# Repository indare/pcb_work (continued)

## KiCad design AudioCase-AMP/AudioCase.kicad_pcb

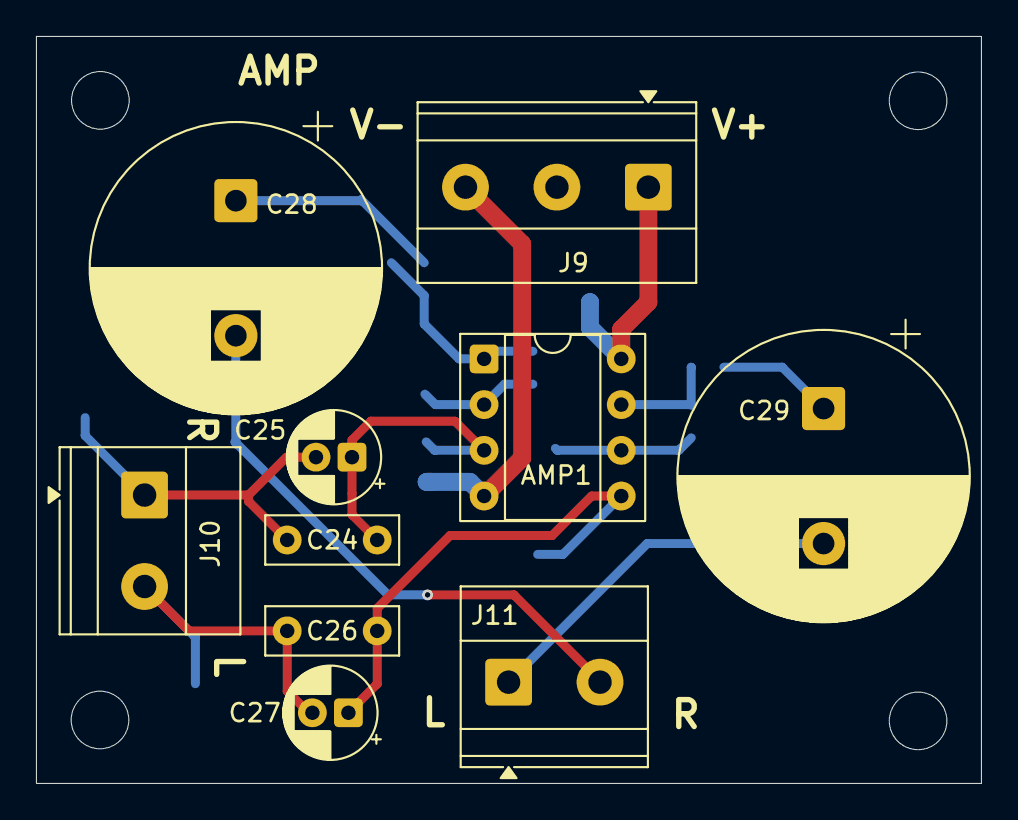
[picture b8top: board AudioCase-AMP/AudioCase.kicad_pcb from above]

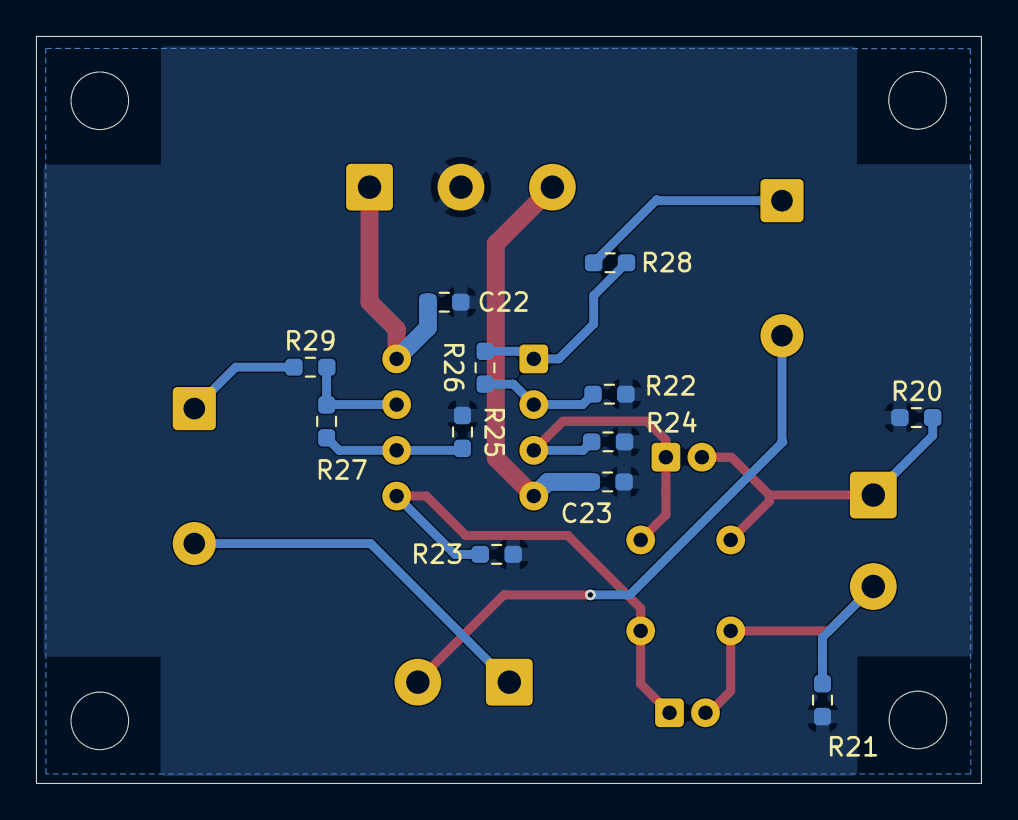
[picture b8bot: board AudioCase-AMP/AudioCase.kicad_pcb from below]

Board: 2 copper layers, 52.5 x 41.5 mm, 26 parts (12 on the bottom side), 15 nets.

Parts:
AMP1: NE5532; DIP-8_W7.62mm_Socket
C22, C23: 0.1μF; R_0603_1608Metric_Pad0.98x0.95mm_HandSolder
C24, C26: 0.1μF; C_Rect_L7.2mm_W2.5mm_P5.00mm_FKS2_FKP2_MKS2_MKP2
C25, C27: 10μF; CP_Radial_D5.0mm_P2.00mm
C28, C29: 470μF; CP_Radial_D16.0mm_P7.50mm
H5, H6, H7, H8: MountingHole; MountingHole_3.2mm_M3
J9: AMP_PWR; TerminalBlock_Phoenix_MKDS-1,5-3-5.08_1x03_P5.08mm_Horizont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
J10: AMP_AUX_IN; TerminalBlock_Phoenix_MKDS-1,5-2-5.08_1x02_P5.08mm_Horizont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
J11: AMP_AUX_OUT; TerminalBlock_Phoenix_MKDS-1,5-2-5.08_1x02_P5.08mm_Horizont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
R20, R21: 220KΩ; R_0603_1608Metric_Pad0.98x0.95mm_HandSolder
R22, R23, R24, R25: 10KΩ; R_0603_1608Metric_Pad0.98x0.95mm_HandSolder
R26, R27: 47KΩ; R_0603_1608Metric_Pad0.98x0.95mm_HandSolder
R28, R29: 50Ω; R_0603_1608Metric_Pad0.98x0.95mm_HandSolder

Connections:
/AmpModule/L_OUT: C29.2, J11.1
/AmpModule/R_OUT: C28.2, J11.2
/Rotary_L_OUT: C26.2, C27.2, J10.2, R21.1
/Rotary_R_OUT: C24.2, C25.2, J10.1, R20.1
/Rotary_V+_OUT: AMP1.8 (V+), C22.2, J9.1
/Rotary_V-_OUT: AMP1.4 (V-), C23.1, J9.3
GND: C22.1, C23.2, J9.2, R20.2, R21.2, R22.1, R23.1, R24.2, R25.1
unnamed: AMP1.1, R26.2, R28.1
unnamed: AMP1.7, R27.2, R29.1
unnamed: AMP1.3 (+), C24.1, C25.1, R24.1
unnamed: AMP1.2 (-), R22.2, R26.1
unnamed: AMP1.5 (+), C26.1, C27.1, R23.2
unnamed: AMP1.6 (-), R25.2, R27.1
unnamed: C28.1, R28.2
unnamed: C29.1, R29.2

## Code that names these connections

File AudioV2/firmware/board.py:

"""AudioV2 Pico ピン／I²C（MeasureControl・FrontPanel のネットに合わせる）。

数値の正は回路図。ここはファームが読むためのコピー。
"""

# I²C0 — PT2314E 同居。OLED が無いので 100 kHz でよい。
I2C_ID = 0
I2C_SDA = 20
I2C_SCL = 21
I2C_FREQ_HZ = 100_000

# FrontPanel MCP23017（UI）。ストラップ固定 **0x22**（娘ジャンパから除外）。
MCP_UI_ADDR = 0x22

# 娘 AmpBank MCP — 基板ジャンパ A2/A1/A0（6 段）。UI 0x22 を飛ばす。
# Bridged12=GND=0 / 2-3 bridge=3V3=1。出荷時オール GND → 0x20。
AMP_ADDR_TIERS = (
    0x20,  # 000 tier1
    0x21,  # 001 tier2
    0x23,  # 011 tier3
    0x24,  # 100 tier4
    0x25,  # 101 tier5
    0x26,  # 110 tier6
)

# ENC INT（MCP OD → Pico）
ENC_INTA = 16
ENC_INTB = 17

# Waveshare LCD SPI0
LCD_CS = 5
LCD_DC = 6
LCD_RST = 7
LCD_EN = 8
LCD_SCK = 18
LCD_MOSI = 19

# タッチ（当面未使用でもピンは確保）
TP_SDA = 10
TP_SCL = 11
TP_INT = 12
TP_RST = 13

# DEST_ADC はラダー廃止済み。読む必要なし（図では D_GND プル）。
DEST_ADC = 26

# Amp バックエンド: "switch" | "relay"（起動時に決める／設定定数）
AMP_BACKEND = "switch"

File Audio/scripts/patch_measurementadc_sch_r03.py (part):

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        text,
        "A3 Pico2: VSYS=+5V_D GND=D_GND | GP0=ADC_DATA GP1=ADC_BCK GP2=ADC_LRCK | "
        "GP3=LCD_SCK GP4=LCD_MOSI GP5=LCD_CS GP6=LCD_DC GP7=LCD_RST GP8=LCD_EN | "
        "GP10=TP_SDA GP11=TP_SCL GP12=TP_INT GP13=TP_RST. Wire labels to pins in EESchema.",
        "A3 Pico2 横置き: 南列 1-20 西→東 / 北列 21-40 東→西。VSYS=+5V_D via D701 ショットキ, GND=D_GND | "
        "GP0=ADC_DATA GP1=ADC_BCK GP2=ADC_LRCK | GP3/GP4=NC(旧 LCD SPI) | "
        "GP5=LCD_CS GP6=LCD_DC GP7=LCD_RST GP8=LCD_EN | GP9=MCLK_SENSE (R720 1k, 入力専用) | "
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    )

    # ---------- 2. LCD SPI: GP3/GP4 -> GP18/GP19 ----------
    text = drop_label(text, "LCD_SCK", X_LEFT_LBL, GP3)
    text = drop_label(text, "LCD_MOSI", X_LEFT_LBL, GP4)
    text = drop_wire(text, X_LEFT, GP3, X_LEFT_LBL, GP3)
    text = drop_wire(text, X_LEFT, GP4, X_LEFT_LBL, GP4)
    text = drop_nc(text, X_RIGHT, GP18)
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        nc(X_LEFT, GP3)
        + nc(X_LEFT, GP4)
        + wire(X_RIGHT, GP18, X_RIGHT_LBL, GP18)
        + label("LCD_SCK", X_RIGHT_LBL, GP18, 0, "left")
        + wire(X_RIGHT, GP19, X_RIGHT_LBL, GP19)
        + label("LCD_MOSI", X_RIGHT_LBL, GP19, 0, "left")
    )

    # ---------- 3. GP15 -> ADC_nRST, GP9 -> MCLK_SENSE, TP701 ----------
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    text = drop_nc(text, X_LEFT, GP9)
    jumpers = (
        wire(X_LEFT, GP15, X_LEFT_LBL, GP15)
        + label("ADC_nRST", X_LEFT_LBL, GP15, 180, "right")
        + wire(X_LEFT, GP9, X_LEFT_LBL, GP9)
        + label("MCLK_SENSE", X_LEFT_LBL, GP9, 180, "right")
    )
    # R720 hangs off the ADC_MCLK net next to Y701/R718; TP701 taps R718 pin 2.
    mclk = (
        junction(430.53, 77.47)
        + wire(430.53, 77.47, 430.53, 71.12)
        + wire(433.07, 77.47, 433.07, 86.36)
        + wire(433.07, 93.98, 433.07, 96.52)
        + label("MCLK_SENSE", 433.07, 96.52, 90, "left")
    )

    # ---------- 4. supervisors: CT 100k to VDD, SENSE caps ----------
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        + wire(389.89, 109.22, 402.59, 109.22)
        + junction(402.59, 109.22)
        + wire(389.89, 101.6, 389.89, 99.06)
        + label("ADC_GND", 389.89, 99.06, 90, "left")
        # U710 (G50 on +5V_A)
        + wire(391.16, 144.78, 402.59, 144.78)
        + label("CT_G50", 396.24, 144.78, 0, "left")
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        + wire(389.89, 139.7, 402.59, 139.7)
        + junction(402.59, 139.7)
        + wire(389.89, 132.08, 389.89, 129.54)
        + label("ADC_GND", 389.89, 129.54, 90, "left")
    )

    text = insert_before(text, r"^\t\(wire\n", power + spi + jumpers + mclk + sup)
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        )
        + symbol(
            "Connector:TestPoint", "TP701", "ADC_MCLK", "TestPoint:TestPoint_Pad_D1.5mm",
            430.53, 71.12, 0, "ADC_MCLK probe pad after R718.", pins=("1",),
            ref_at=(433.07, 68.58, "left"), val_at=(433.07, 66.04, "left"),
            hide_value=True,
        )
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
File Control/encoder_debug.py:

from machine import Pin
import time


ENC_A_PIN = 22
ENC_B_PIN = 26
ENC_SW_PIN = 27

enc_a = Pin(ENC_A_PIN, Pin.IN, Pin.PULL_UP)
enc_b = Pin(ENC_B_PIN, Pin.IN, Pin.PULL_UP)
enc_sw = Pin(ENC_SW_PIN, Pin.IN, Pin.PULL_UP)


def read_state():
    return enc_a.value(), enc_b.value(), enc_sw.value()


last = None
start = time.ticks_ms()
print("encoder debug start: A=GP22 B=GP26 SW=GP27")
print("Turn encoder and press switch for 30 seconds.")

while time.ticks_diff(time.ticks_ms(), start) < 30_000:
    state = read_state()
    if state != last:
        elapsed = time.ticks_diff(time.ticks_ms(), start)
        print(elapsed, "ms", "A", state[0], "B", state[1], "SW", state[2])
        last = state
    time.sleep_ms(10)

print("encoder debug done")
